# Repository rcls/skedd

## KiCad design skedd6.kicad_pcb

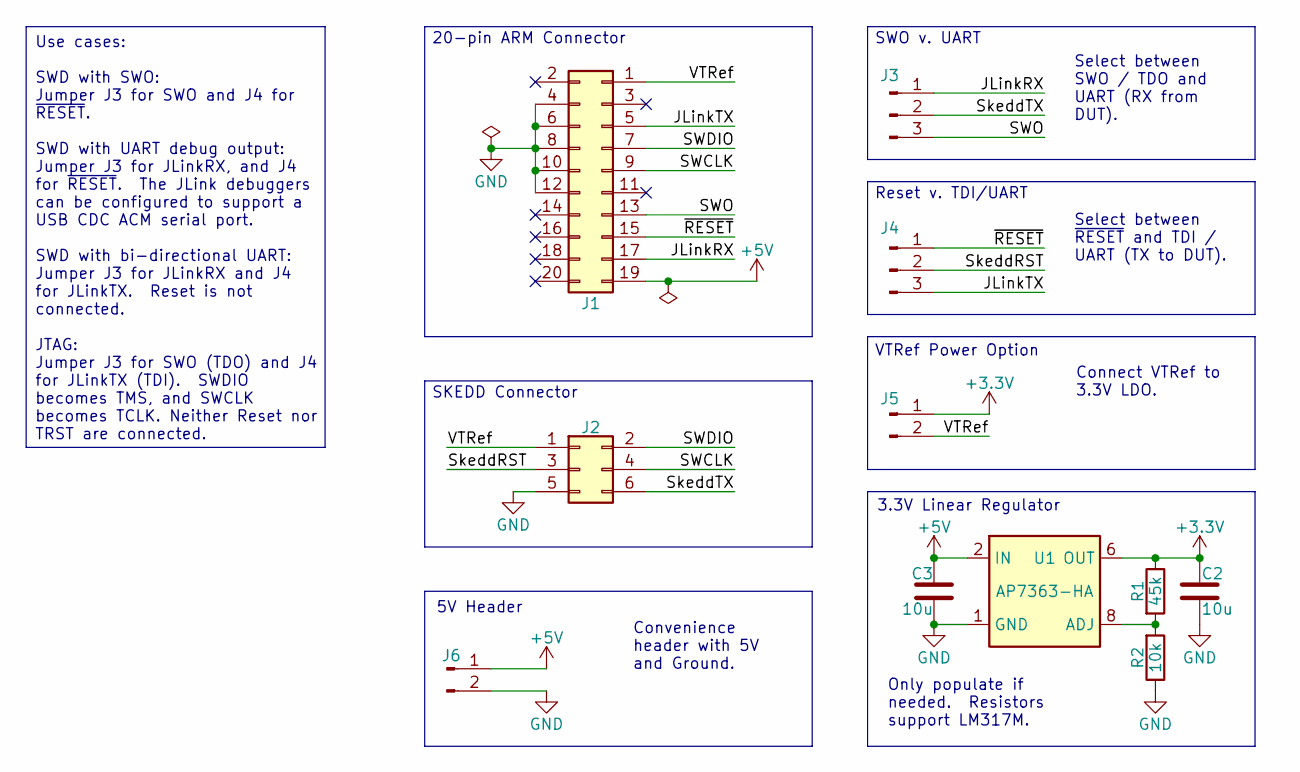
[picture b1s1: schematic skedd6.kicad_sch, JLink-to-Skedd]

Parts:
C2, C3: 10u; C_0603_1608Metric
J1: Conn_02x10_Odd_Even; PinSocket_2x10_P2.54mm_Horizontal
J2: Conn_02x03_Odd_Even; Skedd6
J3, J4: Conn_01x03_Pin; PinHeader_1x03_P2.54mm_Vertical
J5, J6: Conn_01x02_Pin; PinHeader_1x02_P2.54mm_Vertical
R1: 45k; R_0603_1608Metric
R2: 10k; R_0603_1608Metric
U1: AP7363-HA; DFN-8-1EP_3x2mm_P0.5mm_EP1.6x1.5mm

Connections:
+3.3V: C2.2, J5.1, R1.1, U1.5 (OUT), U1.6 (OUT), U1.7 (OUT)
+5V: C3.2, J1.19, J6.1, U1.2 (IN), U1.3 (IN), U1.4 (IN)
/JLinkRX: J1.17, J3.1
/JLinkTX: J1.5, J4.3
/SWCLK: J1.9, J2.4
/SWDIO: J1.7, J2.2
/SWO: J1.13, J3.3
/SkeddRST: J2.3, J4.2
/SkeddTX: J2.6, J3.2
/VTRef: J1.1, J2.1, J5.2
/~RESET: J1.15, J4.1
GND: C2.1, C3.1, J1.4, J1.6, J1.8, J1.10, J1.12, J2.5, J6.2, R2.1, U1.1 (GND), U1.9 (GND)
unnamed: R1.2, R2.2, U1.8 (ADJ)

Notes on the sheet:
SKEDD Connector
3.3V Linear Regulator
5V Header
Reset v. TDI/UART
20-pin ARM Connector
VTRef Power Option
SWO v. UART
Select between SWO / TDO and UART (RX from DUT).
Select between ~{RESET} and TDI / UART (TX to DUT).
Convenience header with 5V and Ground.
Use cases: SWD with SWO: Jumper J3 for SWO and J4 for ~{RESET}. SWD with UART debug output: Jumper J3 for JLinkRX, and J4 for ~{RESET}. The JLink debuggers can be configured to support a USB CDC ACM serial port. SWD with bi-directional UART: Jumper J3 for JLinkRX and J4 for JLinkTX. Reset is not co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
Connect VTRef to 3.3V LDO.
Only populate if needed. Resistors support LM317M.

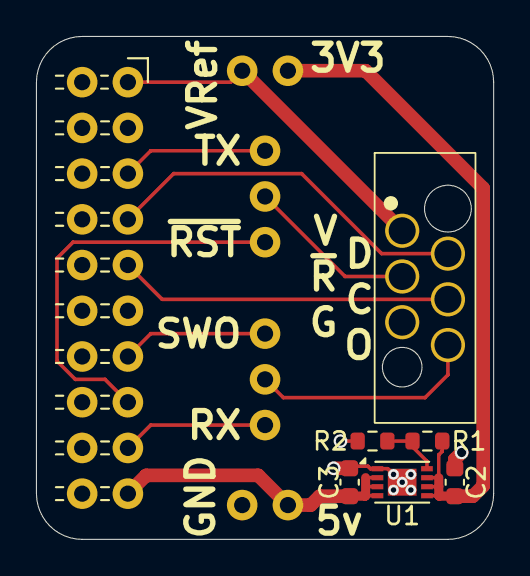
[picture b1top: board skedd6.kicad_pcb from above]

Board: 2 copper layers, 25.4 x 27.9 mm, 11 parts (0 on the bottom side), 13 nets.

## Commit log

2025-12-02 20-pin ARM to 6 pin skedd breakout.
    Has jumper options & optional 3.3v LDO.
2025-12-02 Version with AP7362 LDO
2026-06-17 Skedd6-to-JTAG
2026-06-17 Tweaks.
